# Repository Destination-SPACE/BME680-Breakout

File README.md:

# BME680-Breakout
This breakout board is for the Bosch BME680/688 low power gas, pressure, tempreture, and humidity sensor. This board has a default I2C address of 0x77 and is **3.3V** only.

Requires symbols and footprints from [DS Global Library](https://github.com/Destination-SPACE/DS-KiCad-Global-Source)

# Licnese

Licensed under the CERN OHLv2 - [Permissive](https://github.com/Destination-SPACE/BME680-Breakout/blob/main/LICENSE) or as referenced.

(c) Destination SPACE Inc. 2021

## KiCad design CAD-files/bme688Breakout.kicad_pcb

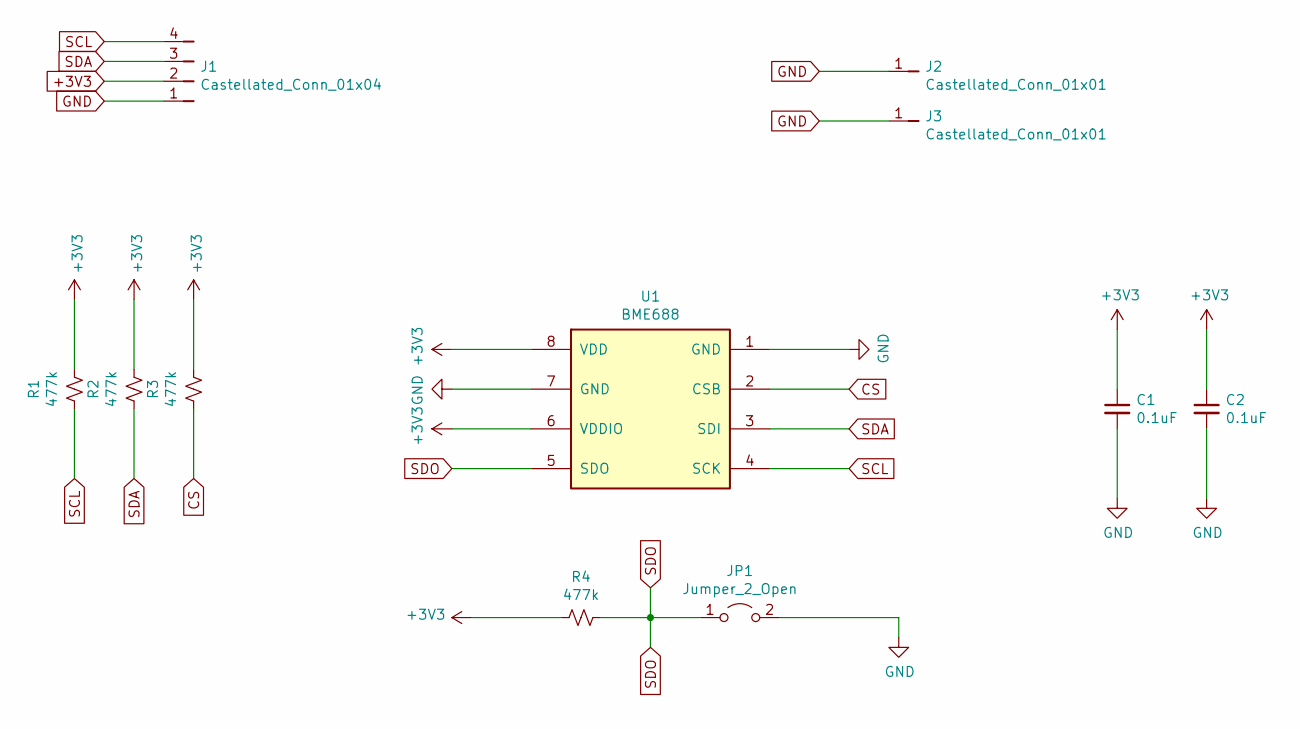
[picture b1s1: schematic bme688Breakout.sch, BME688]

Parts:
C1, C2: 0.1uF; C_0805_2012Metric
J1: Castellated_Conn_01x04; Castellated_PinHeader_01x04_P2.54mm_Vertical
J2, J3: Castellated_Conn_01x01; Castellated_PinHeader_01x01_P2.54mm_Vertical
JP1: Jumper_2_Open; SolderJumper-2_P1.3mm_Open_TrianglePad1.0x1.5mm
R1, R2, R3, R4: 477k; R_0805_2012Metric
U1: BME688; Bosch_LGA-8_3x3mm_P0.8mm_ClockwisePinNumbering

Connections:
+3V3: C1.1, C2.1, J1.2, R1.1, R2.1, R3.1, R4.2, U1.6 (VDDIO), U1.8 (VDD)
CS: R3.2, U1.2 (CSB)
GND: C1.2, C2.2, J1.1, J2.1, J3.1, JP1.2 (B), U1.1 (GND), U1.7 (GND)
SCL: J1.4, R1.2, U1.4 (SCK)
SDA: J1.3, R2.2, U1.3 (SDI)
SDO: JP1.1 (A), R4.1, U1.5 (SDO)

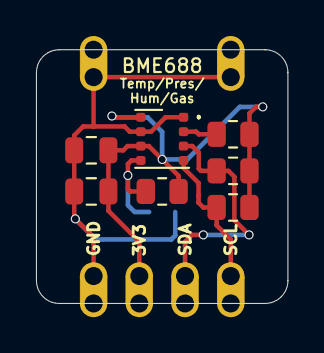
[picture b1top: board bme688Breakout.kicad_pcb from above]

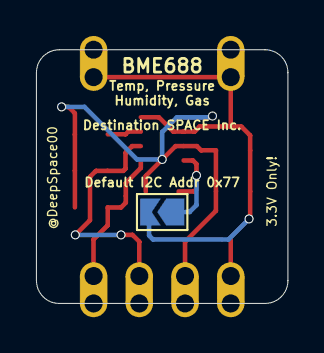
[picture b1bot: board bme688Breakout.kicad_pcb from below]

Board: 2 copper layers, 14.0 x 14.1 mm, 11 parts (2 on the bottom side), 6 nets.

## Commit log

2021-09-14 Create LICENSE
2021-09-28 added castellated holes

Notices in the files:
CAD-files/bme688Breakout.sch:
Licensed under CERN OHLv2 - Permissive
